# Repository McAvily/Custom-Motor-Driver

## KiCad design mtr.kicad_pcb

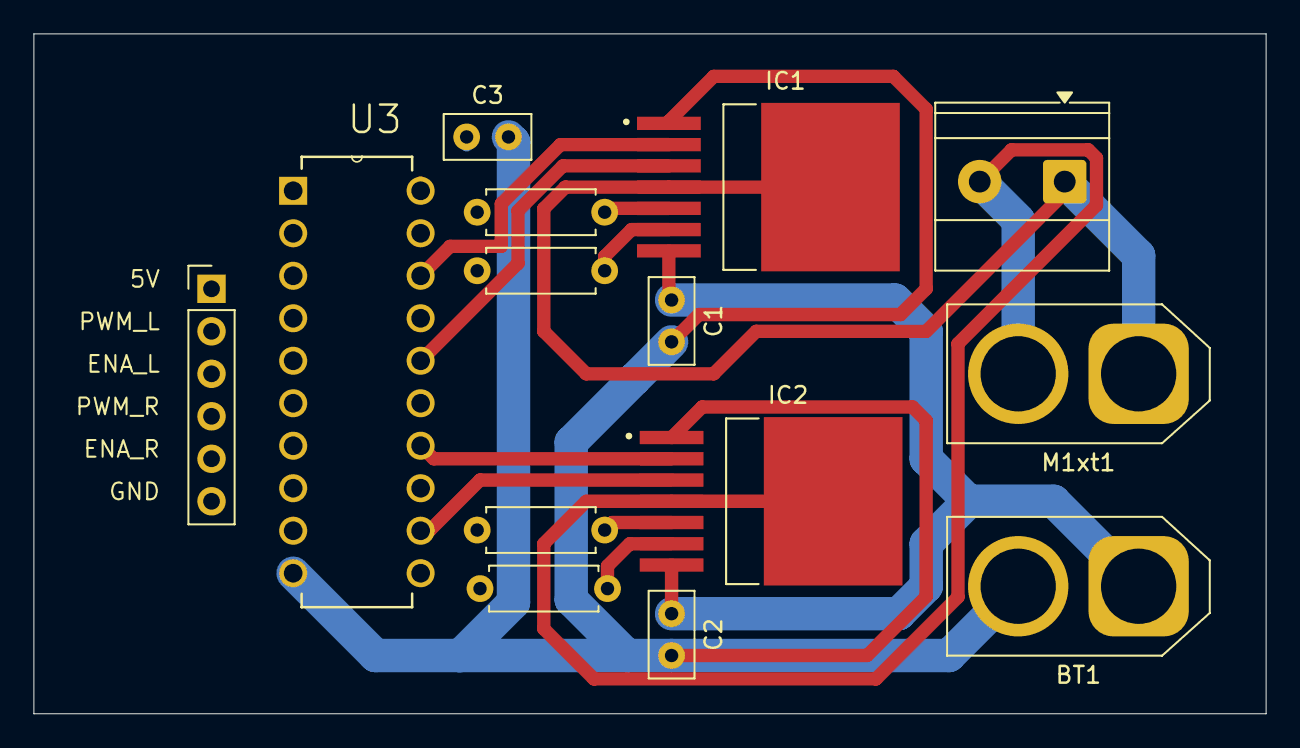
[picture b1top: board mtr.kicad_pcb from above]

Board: 4 copper layers, 73.7 x 40.6 mm, 14 parts (0 on the bottom side), 18 nets.

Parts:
BT1: AMASS_XT60-M_1x02_P7.20mm_Vertical
C1, C2, C3: -; C_Disc_D5.0mm_W2.5mm_P2.50mm
IC1, IC2: DPAK127P1490X440-8N
LogicRail1: PWM_L; PinHeader_1x06_P2.54mm_Vertical
M1sr1: Motor_DC; TerminalBlock_Phoenix_MKDS-1,5-2-5.08_1x02_P5.08mm_Horizont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
M1xt1: Motor_DC; AMASS_XT60-M_1x02_P7.20mm_Vertical
R1, R2, R3, R4: R_Axial_DIN0207_L6.3mm_D2.5mm_P7.62mm_Horizontal
U3: SN74HC244N; DIP254P762X508-20

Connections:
/5V: C3.1, LogicRail1.1, U3.20 (VCC)
unnamed: BT1.1 (+), C1.1, C2.1, IC1.7 (VS), IC2.7 (VS)
unnamed: BT1.2 (-), C1.2, C2.2, C3.2, IC1.1 (GND), IC2.1 (GND), U3.10 (GND)
unnamed: IC1.2 (IN), U3.18 (1Y1)
unnamed: IC1.3 (INH), U3.16 (1Y2)
unnamed: IC1.6 (IS), R3.1
unnamed: IC1.5 (SR), R1.2
unnamed: IC2.2 (IN), U3.14 (1Y3)
unnamed: IC2.3 (INH), U3.12 (1Y4)
unnamed: IC2.6 (IS), R4.1
unnamed: IC2.5 (SR), R2.2
unnamed: LogicRail1.2, U3.2 (1A1)
unnamed: LogicRail1.3, U3.4 (1A2)
unnamed: LogicRail1.4, U3.6 (1A3)
unnamed: LogicRail1.5, U3.8 (1A4)
unnamed: LogicRail1.6, R1.1, R2.1, R3.2, R4.2, U3.1 (1~OE), U3.19 (2~OE)
unnamed: IC1.4 (OUT), IC1.8 (OUT), M1sr1.1 (+), M1xt1.1 (+)
unnamed: IC2.4 (OUT), IC2.8 (OUT), M1sr1.2 (-), M1xt1.2 (-)
